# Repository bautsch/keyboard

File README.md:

# keyboard
# Ortholinear keyboard with normal-sized keys and over-sized knob

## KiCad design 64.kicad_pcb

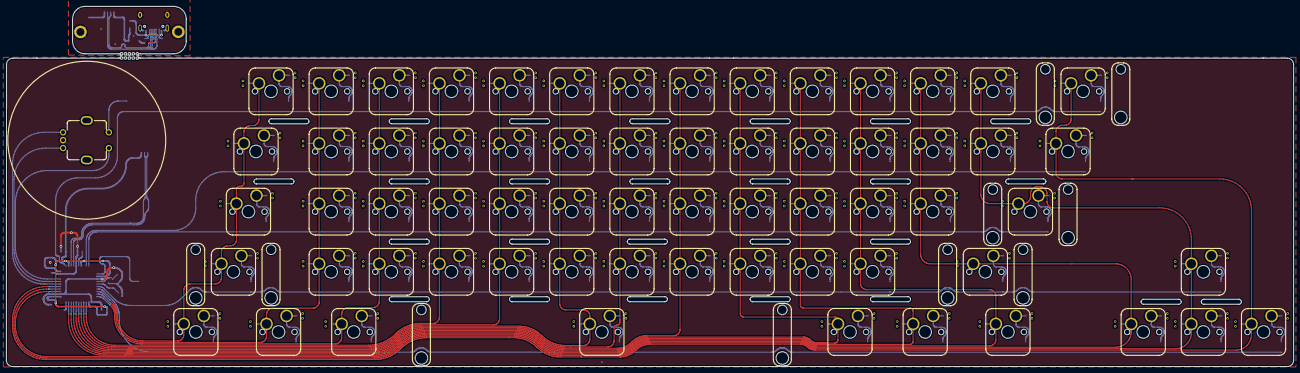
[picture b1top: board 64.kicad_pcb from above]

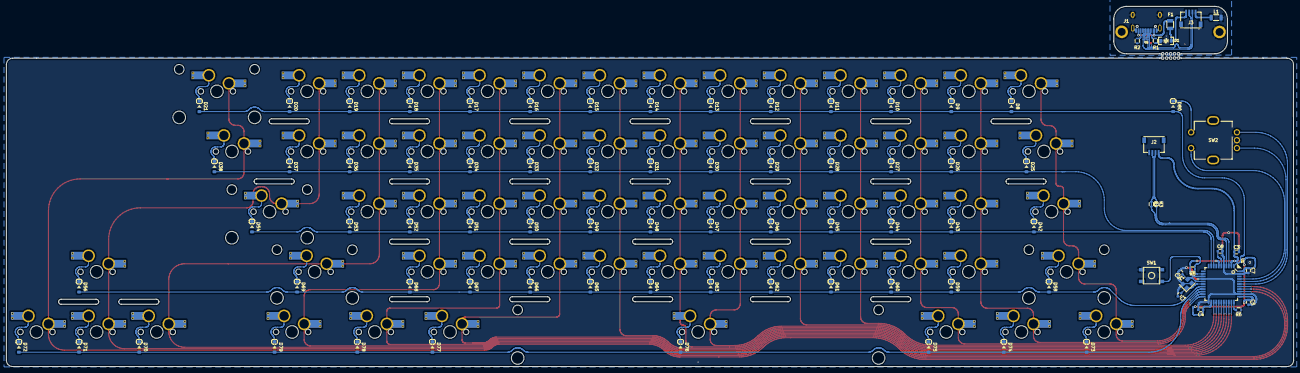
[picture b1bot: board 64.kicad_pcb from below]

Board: 2 copper layers, 407.6 x 114.0 mm, 157 parts (90 on the bottom side), 100 nets.

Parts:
C1, C2: 22pF; C_0603
C3: 10uF; C_0603
C4, C5, C7: 0.1uF; C_0603
C6: 1uF; C_0603
D1: SMF9.0CA; D_SOD-123_Bidirectional
D8, D9, D10, D11, D12, D13, D14, D15, D16, D17, D18, D19, D20, D21, D25, D26, D27, D28, D29, D30, D31, D32, D33, D34, D35, D36, D37, D38, D42, D43, D44, D45, D46, D47, D48, D49, D50, D51, D52, D53, D54, D56, D58, D59, D60, D61, D62, D63, D64, D65, D66, D67, D68, D69, D70, D71, D72, D73, D74, D75, D76, D77, D78, D79, D80: SOD-123; D_SOD-123
F1: Polyfuse; Fuse_SMD1206_Reflow
J1: TYPE-C-31-M12_13; TYPE-C-31-M-12
J2, J3: SM04B-SRSS-TB(LF)(SN); JST_SM04B-SRSS
L1: 60R@100MHz; L_1206_3216Metric
MH1, MH2: Mount - M2; MountingHole_2.5x4.0mm
MX_#0, MX_#1, MX_#2, MX_#3, MX_#4, MX_#5, MX_#6, MX_#7, MX_#8, MX_#9: MX-1U; MXOnly-1U-NoLED-Hotswap-Antishear
MX_'1: MX-1U; MXOnly-1U-NoLED-Hotswap-Antishear
MX_,1: MX-1U; MXOnly-1U-NoLED-Hotswap-Antishear
MX_-1: MX-1U; MXOnly-1U-NoLED-Hotswap-Antishear
MX_.1: MX-1U; MXOnly-1U-NoLED-Hotswap-Antishear
MX_/1: MX-1U; MXOnly-1U-NoLED-Hotswap-Antishear
MX_;1: MX-1U; MXOnly-1U-NoLED-Hotswap-Antishear
MX_=1: MX-1U; MXOnly-1U-NoLED-Hotswap-Antishear
MX_A1: MX-1U; MXOnly-1U-NoLED-Hotswap-Antishear
MX_B1: MX-1U; MXOnly-1U-NoLED-Hotswap-Antishear
MX_BKSPC1: MX-2U; MXOnly-2U-NoLED-Hotswap-Antishear
MX_C1: MX-1U; MXOnly-1U-NoLED-Hotswap-Antishear
MX_CAPS1: MX-1.75U; MXOnly-1.75U-NoLED-Hotswap-Antishear
MX_D1: MX-1U; MXOnly-1U-NoLED-Hotswap-Antishear
MX_DOWN1: MX-1U; MXOnly-1U-NoLED-Hotswap-Antishear
MX_E1: MX-1U; MXOnly-1U-NoLED-Hotswap-Antishear
MX_ENTER1: MX-2.25U; MXOnly-2.25U-NoLED-Hotswap-Antishear
MX_ESC1: MX-1U; MXOnly-1U-NoLED-Hotswap-Antishear
MX_F1: MX-1U; MXOnly-1U-NoLED-Hotswap-Antishear
MX_G1: MX-1U; MXOnly-1U-NoLED-Hotswap-Antishear
MX_H1: MX-1U; MXOnly-1U-NoLED-Hotswap-Antishear
MX_I1: MX-1U; MXOnly-1U-NoLED-Hotswap-Antishear
MX_J1: MX-1U; MXOnly-1U-NoLED-Hotswap-Antishear
MX_K1: MX-1U; MXOnly-1U-NoLED-Hotswap-Antishear
MX_L1: MX-1U; MXOnly-1U-NoLED-Hotswap-Antishear
MX_LALT1: MX-1.25U; MXOnly-1.25U-NoLED-Hotswap-Antishear
MX_LCODE1: MX-1.25U; MXOnly-1.25U-NoLED-Hotswap-Antishear
MX_LCTRL1: MX-1.5U; MXOnly-1.5U-NoLED-Hotswap-Antishear
MX_LEFT1: MX-1U; MXOnly-1U-NoLED-Hotswap-Antishear
MX_LSHIFT1: MX-2.25U; MXOnly-2.25U-NoLED-Hotswap-Antishear
MX_M1: MX-1U; MXOnly-1U-NoLED-Hotswap-Antishear
MX_N1: MX-1U; MXOnly-1U-NoLED-Hotswap-Antishear
MX_O1: MX-1U; MXOnly-1U-NoLED-Hotswap-Antishear
MX_P1: MX-1U; MXOnly-1U-NoLED-Hotswap-Antishear
MX_Q1: MX-1U; MXOnly-1U-NoLED-Hotswap-Antishear
MX_R1: MX-1U; MXOnly-1U-NoLED-Hotswap-Antishear
MX_RALT1: MX-1.25U; MXOnly-1.25U-NoLED-Hotswap-Antishear
MX_RCODE1: MX-1.25U; MXOnly-1.25U-NoLED-Hotswap-Antishear
MX_RCTRL1: MX-1.5U; MXOnly-1.5U-NoLED-Hotswap-Antishear
MX_RIGHT1: MX-1U; MXOnly-1U-NoLED-Hotswap-Antishear
MX_RSHIFT1: MX-2.75U; MXOnly-2.75U-NoLED-Hotswap-Antishear
MX_S1: MX-1U; MXOnly-1U-NoLED-Hotswap-Antishear
MX_SPACE1: MX-7U; MXOnly-7U-NoLED-Hotswap-Antishear
MX_T1: MX-1U; MXOnly-1U-NoLED-Hotswap-Antishear
MX_TAB1: MX-1.5U; MXOnly-1.5U-NoLED-Hotswap-Antishear
MX_U1: MX-1U; MXOnly-1U-NoLED-Hotswap-Antishear
MX_UP1: MX-1U; MXOnly-1U-NoLED-Hotswap-Antishear
MX_V1: MX-1U; MXOnly-1U-NoLED-Hotswap-Antishear
MX_W1: MX-1U; MXOnly-1U-NoLED-Hotswap-Antishear
MX_X1: MX-1U; MXOnly-1U-NoLED-Hotswap-Antishear
MX_Y1: MX-1U; MXOnly-1U-NoLED-Hotswap-Antishear
MX_Z1: MX-1U; MXOnly-1U-NoLED-Hotswap-Antishear
MX_[1: MX-1U; MXOnly-1U-NoLED-Hotswap-Antishear
MX_\1: MX-1.5U; MXOnly-1.5U-NoLED-Hotswap-Antishear
MX_]1: MX-1U; MXOnly-1U-NoLED-Hotswap-Antishear
R1, R2: 5.1k; R_0603
R3, R4: 22; R_0603
R5: 10k; R_0603
R6: 1k; R_0603
SW1: SW_Push; SKQG-1155865
SW2: Rotary_Encoder_Switch; ALPS_EC11E
U1: ATMEGA32U4; TQPF-44_10x10mm_P0.8mm
U2: TPD4E05U06DQAR; USON-10_2.5x1.0mm_P0.5mm
Y1: 16MHz; Crystal_SMD_3225-4pin_3.2x2.5mm
svg2mod, svg2mod#2: G***; violetta76_main

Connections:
+5V: C3.1, C4.1, C5.1, C7.1, D1.1, F1.1, J2.1, J3.1, R5.2, U1.2, U1.7, U1.14, U1.24, U1.34, U1.44
COL0: SW2.S1, U1.41
COL1: MX_CAPS1.1, MX_ESC1.1, MX_LCTRL1.1, MX_LSHIFT1.1, MX_TAB1.1, U1.20
COL2: MX_#1.1, MX_A1.1, MX_LCODE1.1, MX_Q1.1, MX_Z1.1, U1.21
COL3: MX_#2.1, MX_LALT1.1, MX_S1.1, MX_W1.1, MX_X1.1, U1.22
COL4: MX_#3.1, MX_C1.1, MX_D1.1, MX_E1.1, U1.25
COL5: MX_#4.1, MX_F1.1, MX_R1.1, MX_V1.1, U1.26
COL6: MX_#5.1, MX_B1.1, MX_G1.1, MX_SPACE1.1, MX_T1.1, U1.27
COL7: MX_#6.1, MX_H1.1, MX_N1.1, MX_Y1.1, U1.28
COL8: MX_#7.1, MX_J1.1, MX_M1.1, MX_U1.1, U1.29
COL9: MX_#8.1, MX_,1.1, MX_I1.1, MX_K1.1, MX_RALT1.1, U1.30
COL10: MX_#9.1, MX_.1.1, MX_L1.1, MX_O1.1, MX_RCODE1.1, U1.31
COL11: MX_#0.1, MX_/1.1, MX_;1.1, MX_P1.1, MX_RCTRL1.1, U1.32
COL12: MX_'1.1, MX_-1.1, MX_LEFT1.1, MX_RSHIFT1.1, MX_[1.1, U1.36
COL13: MX_=1.1, MX_DOWN1.1, MX_ENTER1.1, MX_UP1.1, MX_]1.1, U1.37
COL14: MX_BKSPC1.1, MX_RIGHT1.1, MX_\1.1, U1.38
DA+: J1.A6, J1.B6, J2.3, J3.3, R4.1, R4.2, U1.4, U2.1, U2.4, U2.7, U2.10
DA-: J1.A7, J1.B7, J2.2, J3.2, R3.1, R3.2, U1.3, U2.2, U2.5, U2.6, U2.9
EN_A: SW2.A, U1.40
EN_B: SW2.B, U1.39
GND: C1.2, C2.2, C3.2, C4.2, C5.2, C6.2, C7.2, J2.4, J3.4, L1.1, R6.1, SW1.1, SW2.C, U1.5, U1.15, U1.23, U1.35, U1.43, Y1.2, Y1.4
GNDPWR: D1.2, J1.A1, J1.B1, J1.S, L1.2, MH2.1, R1.1, R2.1, U2.3, U2.8
unnamed: C6.1, U1.6
unnamed: D8.1, MX_ESC1.2
unnamed: D9.1, MX_#1.2
unnamed: D10.1, MX_#2.2
unnamed: D11.1, MX_#3.2
unnamed: D12.1, MX_#4.2
unnamed: D13.1, MX_#5.2
unnamed: D14.1, MX_#6.2
unnamed: D15.1, MX_#7.2
unnamed: D16.1, MX_#8.2
unnamed: D17.1, MX_#9.2
unnamed: D18.1, MX_#0.2
unnamed: D19.1, MX_-1.2
unnamed: D20.1, MX_=1.2
unnamed: D21.1, MX_BKSPC1.2
unnamed: D25.1, MX_TAB1.2
unnamed: D26.1, MX_Q1.2
unnamed: D27.1, MX_W1.2
unnamed: D28.1, MX_E1.2
unnamed: D29.1, MX_R1.2
unnamed: D30.1, MX_T1.2
unnamed: D31.1, MX_Y1.2
unnamed: D32.1, MX_U1.2
unnamed: D33.1, MX_I1.2
unnamed: D34.1, MX_O1.2
unnamed: D35.1, MX_P1.2
unnamed: D36.1, MX_[1.2
unnamed: D37.1, MX_]1.2
unnamed: D38.1, MX_\1.2
unnamed: D42.1, MX_CAPS1.2
unnamed: D43.1, MX_A1.2
unnamed: D44.1, MX_S1.2
unnamed: D45.1, MX_D1.2
unnamed: D46.1, MX_F1.2
unnamed: D47.1, MX_G1.2
unnamed: D48.1, MX_H1.2
unnamed: D49.1, MX_J1.2
unnamed: D50.1, MX_K1.2
unnamed: D51.1, MX_L1.2
unnamed: D52.1, MX_;1.2
unnamed: D53.1, MX_'1.2
unnamed: D54.1, MX_ENTER1.2
unnamed: D56.1, MX_UP1.2
unnamed: D58.1, MX_LSHIFT1.2
unnamed: D59.1, MX_Z1.2
unnamed: D60.1, MX_X1.2
unnamed: D61.1, MX_C1.2
unnamed: D62.1, MX_V1.2
unnamed: D63.1, MX_B1.2
unnamed: D64.1, MX_N1.2
unnamed: D65.1, MX_M1.2
unnamed: D66.1, MX_,1.2
unnamed: D67.1, MX_.1.2
unnamed: D68.1, MX_/1.2
unnamed: D69.1, MX_RSHIFT1.2
unnamed: D70.1, MX_LEFT1.2
unnamed: D71.1, MX_DOWN1.2
unnamed: D72.1, MX_RIGHT1.2
unnamed: D73.1, MX_LCTRL1.2
unnamed: D74.1, MX_LCODE1.2
unnamed: D75.1, MX_LALT1.2
unnamed: D76.1, MX_SPACE1.2
unnamed: D77.1, MX_RALT1.2
unnamed: D78.1, MX_RCODE1.2
unnamed: D79.1, MX_RCTRL1.2
unnamed: D80.1, SW2.S2
unnamed: J1.A5, R1.2
unnamed: J1.B5, R2.2
unnamed: R5.1, SW1.2, U1.13
unnamed: R6.2, U1.33
ROW0: D8.2, D9.2, D10.2, D11.2, D12.2, D13.2, D14.2, D15.2, D16.2, D17.2, D18.2, D19.2, D20.2, D21.2, D80.2, U1.1
ROW1: D25.2, D26.2, D27.2, D28.2, D29.2, D30.2, D31.2, D32.2, D33.2, D34.2, D35.2, D36.2, D37.2, D38.2, U1.9
ROW2: D42.2, D43.2, D44.2, D45.2, D46.2, D47.2, D48.2, D49.2, D50.2, D51.2, D52.2, D53.2, D54.2, U1.10
ROW3: D56.2, D58.2, D59.2, D60.2, D61.2, D62.2, D63.2, D64.2, D65.2, D66.2, D67.2, D68.2, D69.2, U1.18
ROW4: D70.2, D71.2, D72.2, D73.2, D74.2, D75.2, D76.2, D77.2, D78.2, D79.2, U1.19
VBUS: F1.2, J1.A4, J1.B4
XTAL1: C1.1, U1.17, Y1.1
XTAL2: C2.1, U1.16, Y1.3
